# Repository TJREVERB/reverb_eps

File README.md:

# stopgap-eps
 Stopgap EPS design for TJREVERB (Not to be used as flight hardware)

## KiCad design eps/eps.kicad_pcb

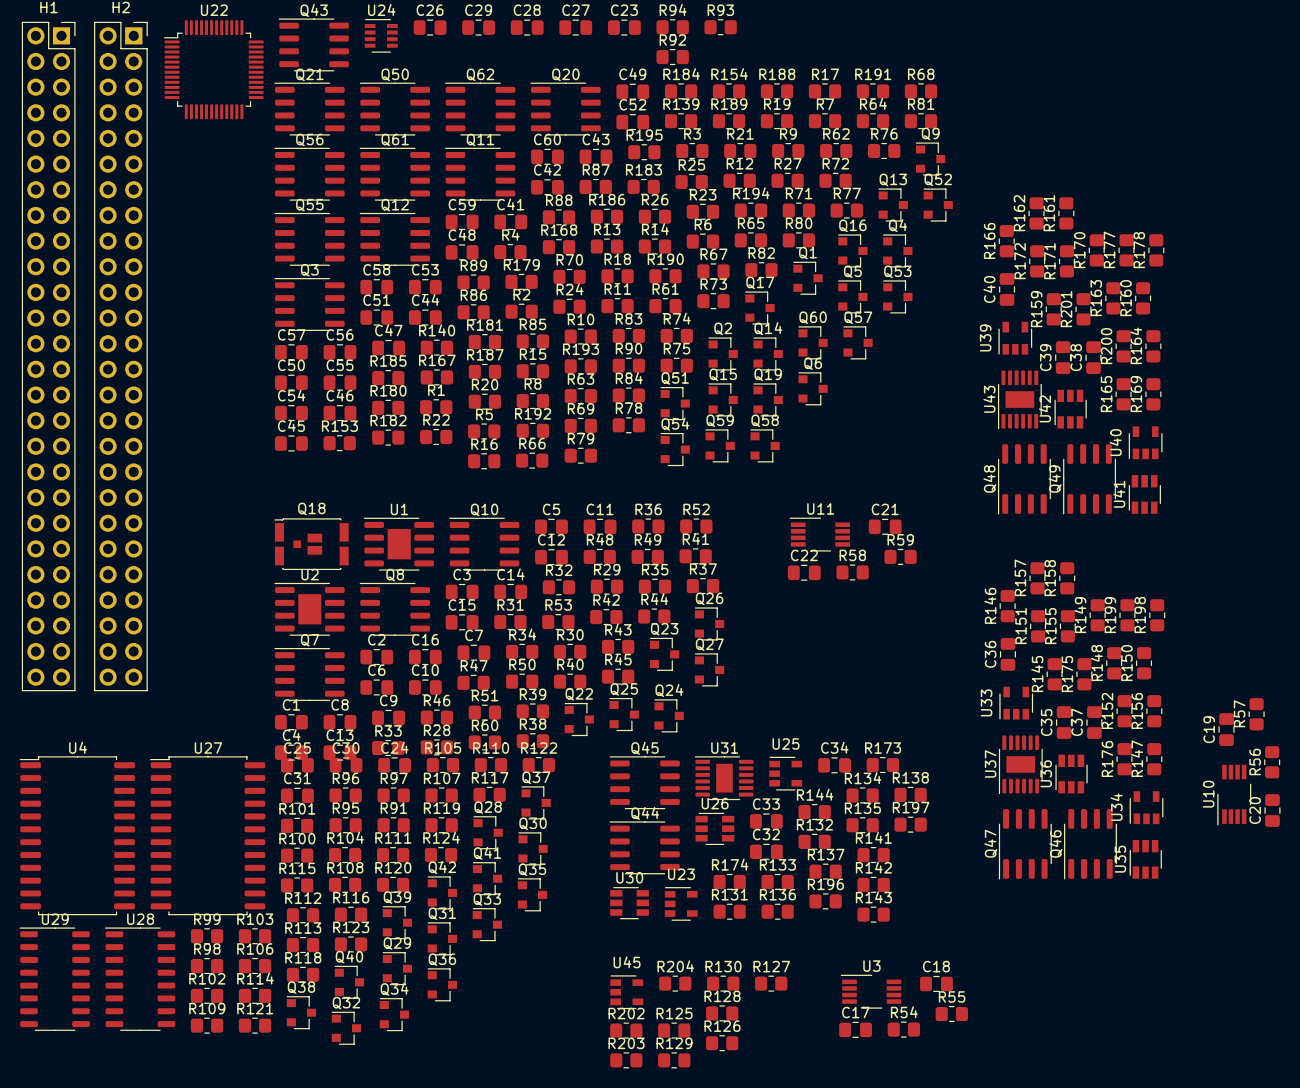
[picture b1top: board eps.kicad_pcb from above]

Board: 2 copper layers, 355 parts (0 on the bottom side), 259 nets, no tracks yet.

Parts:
C1, C2, C9, C10, C18, C20, C22, C32, C34, C35, C37, C38, C40: 10uF; C_0805_2012Metric_Pad1.18x1.45mm_HandSolder
C3, C4, C12, C13, C16, C23, C24, C25, C26, C28, C30, C31, C44, C45, C46, C50, C51, C52, C55, C56, C59, C60: 0.1uF; C_0805_2012Metric_Pad1.18x1.45mm_HandSolder
C5, C6, C7: 47uF; C_0805_2012Metric_Pad1.18x1.45mm_HandSolder
C8: 100uF; C_0805_2012Metric_Pad1.18x1.45mm_HandSolder
C11, C14, C15, C27, C29, C33, C36, C39, C41, C42, C43, C47, C48, C49, C53, C54, C57, C58: 1uF; C_0805_2012Metric_Pad1.18x1.45mm_HandSolder
C17, C19, C21: 0.01uF; C_0805_2012Metric_Pad1.18x1.45mm_HandSolder
H1: EPS Stack Header 2; PinSocket_2x26_P2.54mm_Vertical
H2: EPS Stack Header 1; PinSocket_2x26_P2.54mm_Vertical
Q1, Q2, Q4, Q5, Q6, Q9, Q13, Q14, Q15, Q16, Q17, Q19, Q22, Q23, Q24, Q25, Q26, Q27, Q51, Q52, Q53, Q54, Q57, Q58, Q59, Q60: 2N7002; SOT-23
Q3, Q7, Q8, Q10, Q11, Q12, Q20, Q21, Q43, Q44, Q45, Q46, Q47, Q48, Q49, Q50, Q55, Q56, Q61, Q62: IRF7425; SOIC-8_3.9x4.9mm_P1.27mm
Q18: IRF8302M; DirectFET_MX
Q28, Q29, Q30, Q31, Q32, Q33, Q34, Q35, Q36, Q37, Q38, Q39, Q40, Q41, Q42: IRLML6344; SOT-23
R1, R2, R4, R24, R25, R26, R82, R83, R133, R134, R147, R148, R161, R162, R180, R181, R203: 100R; R_0805_2012Metric_Pad1.20x1.40mm_HandSolder
R3, R5, R6, R7, R8, R9, R10, R11, R12, R18, R19, R20, R21, R22, R23, R27, R32, R33, R36, R37, R38, R41, R42, R46, R48, R49, R50, R51, R52, R53, R60, R62, R63, R64, R65, R66, R67, R68, R69, R76, R77, R78, R79, R80, R81, R84, R85, R86, R87, R88, R89, R92, R94, R154, R167, R168, R179, R182, R183, R184, R185, R186, R187, R192, R193, R194, R195: 10K; R_0805_2012Metric_Pad1.20x1.40mm_HandSolder
R13, R14, R43, R44, R61, R70, R71, R72, R90, R139, R188, R189: 15m; R_0805_2012Metric_Pad1.20x1.40mm_HandSolder
R15, R16, R17, R73, R74, R75, R140, R153, R190, R191: 15K; R_0805_2012Metric_Pad1.20x1.40mm_HandSolder
R28: 322K; R_0805_2012Metric_Pad1.20x1.40mm_HandSolder
R29: 678K; R_0805_2012Metric_Pad1.20x1.40mm_HandSolder
R30: 11.2M; R_0805_2012Metric_Pad1.20x1.40mm_HandSolder
R31, R39, R40, R91, R125, R126, R127, R128, R129, R130, R197, R199, R201: 100K; R_0805_2012Metric_Pad1.20x1.40mm_HandSolder
R34: 10m; R_0805_2012Metric_Pad1.20x1.40mm_HandSolder
R35: 40K; R_0805_2012Metric_Pad1.20x1.40mm_HandSolder
R45, R47: 27K; R_0805_2012Metric_Pad1.20x1.40mm_HandSolder
R54, R56, R58: 5K; R_0805_2012Metric_Pad1.20x1.40mm_HandSolder
R55, R57, R59: 45.5K; R_0805_2012Metric_Pad1.20x1.40mm_HandSolder
R93: 50K; R_0805_2012Metric_Pad1.20x1.40mm_HandSolder
R95, R99, R109, R111: 2.7K; R_0805_2012Metric_Pad1.20x1.40mm_HandSolder
R96, R98, R100, R102, R104, R106, R108, R110, R112, R114, R116, R118, R120, R122, R124, R135, R136, R149, R150, R163, R164, R204: 1K; R_0805_2012Metric_Pad1.20x1.40mm_HandSolder
R97, R105, R107: 3.9K; R_0805_2012Metric_Pad1.20x1.40mm_HandSolder
R101, R103, R113, R115, R117, R119, R121, R123: 1.2K; R_0805_2012Metric_Pad1.20x1.40mm_HandSolder
R131, R132, R145, R146, R159, R160, R202: 20m; R_0805_2012Metric_Pad1.20x1.40mm_HandSolder
R137, R138, R151, R152, R165, R166: 470K; R_0805_2012Metric_Pad1.20x1.40mm_HandSolder
R141, R155, R169: 52.8K; R_0805_2012Metric_Pad1.20x1.40mm_HandSolder
R142, R156, R170: 490K; R_0805_2012Metric_Pad1.20x1.40mm_HandSolder
R143, R157, R171: 330K; R_0805_2012Metric_Pad1.20x1.40mm_HandSolder
R144, R158, R172: 50m; R_0805_2012Metric_Pad1.20x1.40mm_HandSolder
R173, R174, R175, R176, R177, R178, R196, R198, R200: R; R_0805_2012Metric_Pad1.20x1.40mm_HandSolder
U1: ADP2303ARDZ-3.3; SOIC-8-1EP_3.9x4.9mm_P1.27mm_EP2.29x3mm
U2: ADP2303ARDZ-5.0; SOIC-8-1EP_3.9x4.9mm_P1.27mm_EP2.29x3mm
U3, U10, U11: TLC555xPS; VSSOP-8_3.0x3.0mm_P0.65mm
U4, U27: CD74HC4067M; SOIC-24W_7.5x15.4mm_P1.27mm
U22: STM32F103C8Tx; LQFP-48_7x7mm_P0.5mm
U23, U25, U33, U34, U39, U40, U45: LT6106; SOT-23-5
U24: MAX6369; SOT-23-8
U26, U30, U35, U36, U41, U42: LTC4412xS6; TSOT-23-6
U28, U29: 74HC595; SO-16_3.9x9.9mm_P1.27mm
U31, U37, U43: LT3652EMSE; MSOP-12-1EP_3x4mm_P0.65mm_EP1.65x2.85mm

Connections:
3V3RAW: C5.1, C7.1, C23.1, C24.1, C25.1, C26.1, C27.1, C30.1, C31.1, Q10.1, Q10.2, Q10.3, Q43.4, R50.1, R92.1, R94.1, U1.5, U4.24, U22.1, U22.24, U22.36, U22.48, U24.5, U24.6, U24.8, U27.24, U28.10, U28.16, U29.10, U29.16
3V3RESETPLS: R54.2, U3.2
5VRESETPLS: R56.2, U10.2
+3V3: H2.27, H2.28, Q12.1, Q12.2, Q12.3, Q50.1, Q50.2, Q50.3, Q62.1, Q62.2, Q62.3, R12.1, R44.1, R69.1, R103.1, R187.1
+5V: H2.25, H2.26, Q11.1, Q11.2, Q11.3, Q21.1, Q21.2, Q21.3, Q56.1, Q56.2, Q56.3, R11.1, R43.1, R68.1, R89.1, R101.1
+12V: H2.23, H2.24, Q3.1, Q3.2, Q3.3, Q20.1, Q20.2, Q20.3, R5.1, R67.1, R97.1
+BATT: H2.45, H2.46, Q55.1, Q55.2, Q55.3, Q61.1, Q61.2, Q61.3, R34.1, R88.1, R99.1, R186.1
/AnalogTelemetry/AMUX: U4.1, U27.1
/AnalogTelemetry/BRDTMP: R91.1, U27.16
/AnalogTelemetry/EN1: Q28.1, U28.15
/AnalogTelemetry/EN2: Q29.1, U28.1
/AnalogTelemetry/EN3: Q30.1, U28.2
/AnalogTelemetry/EN4: Q31.1, U28.3
/AnalogTelemetry/EN5: Q32.1, U28.4
/AnalogTelemetry/EN6: Q33.1, U28.5
/AnalogTelemetry/EN7: Q34.1, U28.6
/AnalogTelemetry/EN8: Q35.1, U28.7
/AnalogTelemetry/EN9: Q36.1, U29.15
/AnalogTelemetry/EN10: Q37.1, U29.1
/AnalogTelemetry/EN11: Q38.1, U29.2
/AnalogTelemetry/EN12: Q39.1, U29.3
/AnalogTelemetry/EN13: Q40.1, U29.4
/AnalogTelemetry/EN14: Q41.1, U29.5
/AnalogTelemetry/EN15: Q42.1, U29.6
/AnalogTelemetry/RCLK: U28.12, U29.12
/AnalogTelemetry/SEL0: U4.10, U27.10
/AnalogTelemetry/SEL1: U4.11, U27.11
/AnalogTelemetry/SEL2: U4.14, U27.14
/AnalogTelemetry/SEL3: U4.13, U27.13
/AnalogTelemetry/SRCLK: U28.11, U29.11
/AnalogTelemetry/VBCR_OUT: R95.2, R96.1, U4.9
/AnalogTelemetry/VPCM3V3: R103.2, R104.1, U4.5
/AnalogTelemetry/VPCM5V: R101.2, R102.1, U4.6
/AnalogTelemetry/VPCM12V: R97.2, R98.1, U4.8
/AnalogTelemetry/VPCMBATV: R99.2, R100.1, U4.7
/AnalogTelemetry/VSW1: R105.2, R106.1, U4.4
/AnalogTelemetry/VSW2: R107.2, R108.1, U4.3
/AnalogTelemetry/VSW3: R109.2, R110.1, U4.2
/AnalogTelemetry/VSW4: R111.2, R112.1, U4.23
/AnalogTelemetry/VSW5: R113.2, R114.1, U4.22
/AnalogTelemetry/VSW6: R115.2, R116.1, U4.21
/AnalogTelemetry/VSW7: R117.2, R118.1, U4.20
/AnalogTelemetry/VSW8: R119.2, R120.1, U4.19
/AnalogTelemetry/VSW9: R121.2, R122.1, U4.18
/AnalogTelemetry/VSW10: R123.2, R124.1, U4.17
/BCR/SA1AV: R131.2, R133.2, U23.5
/BCR/SA1BV: R132.2, R134.2, U25.5
/BCR/SA2AV: R145.2, R147.2, U33.5
/BCR/SA2BV: R146.2, R148.2, U34.5
/BCR/SA3AV: R159.2, R161.2, U39.5
/BCR/SA3BV: R160.2, R162.2, U40.5
/HNDSHK: R93.1, U22.19, U24.1
/PCM/3v3gate: Q25.1, U3.3
/PCM/5VGATE: Q26.1, U10.3
/PCM/BATGATE: Q27.1, R60.1, U11.3
/RESET: R94.2, U22.7, U22.18, U24.7
/TSET: R92.2, U22.39, U24.4
BATRESETPLS: R58.2, U11.2
BCR1ASTAT: R137.2, U26.4
BCR1BSTAT: R138.2, U30.4
BCR1OUT: C34.1, C37.1, C40.1, R142.1, R144.1, R156.1, R158.1, R170.1, R172.1, R202.2, R203.2, U31.9, U37.9, U43.9, U45.5
BCR2ASTAT: R151.2, U35.4
BCR2BSTAT: R152.2, U36.4
BCR3ASTAT: R165.2, U41.4
BCR3BSTAT: R166.2, U42.4
BCR_OUT: H2.41, H2.42, H2.43, H2.44, R95.1, R202.1, U45.4
GND: C1.2, C2.2, C5.2, C6.2, C7.2, C8.2, C9.2, C10.2, C11.2, C12.2, C13.2, C14.2, C15.2, C16.2, C17.2, C18.2, C19.2, C20.2, C21.2, C22.2, C23.2, C24.2, C25.2, C26.2, C27.2, C28.2, C29.2, C30.2, C31.2, C32.2, C34.2, C35.2, C37.2, C38.2, C40.2, C41.2, C42.2, C43.2, C44.1, C45.1, C46.1, C47.2, C48.2, C49.2, C50.1, C51.1, C52.1, C53.2, C54.2, C55.1, C56.1, C57.2, C58.2, C59.1, C60.1, H2.9, H2.14, H2.17, H2.21, H2.22, H2.29, H2.30, H2.32, H2.47, H2.48, Q2.2, Q5.2, Q9.2, Q14.2, Q16.2, Q19.2, Q22.2, Q23.2, Q24.2, Q25.2, Q27.2, Q28.2, Q29.2, Q30.2, Q31.2, Q32.2, Q33.2, Q34.2, Q35.2, Q36.2, Q37.2, Q38.2, Q39.2, Q40.2, Q41.2, Q42.2, Q52.2, Q54.2, Q58.2, Q60.2, R3.2, R6.2, R7.2, R21.2, R22.2, R23.2, R27.2, R28.2, R36.2, R46.2, R48.2, R60.2, R62.2, R63.2, R79.2, R80.2, R81.2, R84.2, R85.2, R91.2, R93.2, R135.2, R136.2, R143.2, R149.2, R150.2, R157.2, R163.2, R164.2, R168.2, R171.2, R179.2, R182.2, R183.2, R194.2, R195.2, R197.2, R199.2, R201.2, R204.2, U1.7, U1.9, U2.7, U2.9, U3.1, U4.12, U10.1, U11.1, U22.8, U22.23, U22.35, U22.47, U23.2, U24.2, U25.2, U26.2, U26.3, U27.12, U28.8, U28.13, U29.8, U29.13, U30.2, U30.3, U31.6, U31.13, U33.2, U34.2, U35.2, U35.3, U36.2, U36.3, U37.6, U37.13, U39.2, U40.2, U41.2, U41.3, U42.2, U42.3, U43.6, U43.13, U45.2
I3V3: R47.1, U27.5
I5V: R45.1, U27.6
IBATV: R35.1, U27.7
IBCR1A: R135.1, U23.1
IBCR1B: R136.1, U25.1
IBCR2A: R149.1, U33.1
IBCR2B: R150.1, U34.1
IBCR3A: R163.1, U39.1
IBCR3B: R164.1, U40.1
IBCR_OUT: R204.1, U27.9, U45.1
ISW1: R15.1, U27.4
ISW2: R73.1, U27.3
ISW3: R140.1, U27.2
ISW4: R190.1, U27.23
ISW5: R16.1, U27.22
ISW6: R74.1, U27.21
ISW7: R153.1, U27.20
ISW8: R191.1, U27.19
ISW9: R17.1, U27.18
ISW10: R75.1, U27.17
unnamed: C3.1, U1.1
unnamed: C3.2, U1.8
unnamed: C4.1, U2.1
unnamed: C4.2, U2.8
unnamed: C6.1, Q8.1, Q8.2, Q8.3, R49.1, U2.5
unnamed: C17.1, U3.5
unnamed: C18.1, R55.2, U3.6, U3.7
unnamed: C19.1, U10.5
unnamed: C20.1, R57.2, U10.6, U10.7
unnamed: C21.1, U11.5
unnamed: C22.1, R59.2, U11.6, U11.7
unnamed: C33.1, U31.12
unnamed: C33.2, U31.11
unnamed: C36.1, U37.12
unnamed: C36.2, U37.11
unnamed: C39.1, U43.12
unnamed: C39.2, U43.11
unnamed: R144.2, U31.10
unnamed: R158.2, U37.10
unnamed: R172.2, U43.10
unnamed: Q1.1, R1.1, R3.1
unnamed: Q1.2, Q2.3
unnamed: Q1.3, Q3.4, R5.2
unnamed: Q2.1, R8.2
unnamed: Q3.5, Q3.6, Q3.7, Q3.8, R61.2
unnamed: Q4.1, R2.1, R6.1
unnamed: Q4.2, Q5.3
unnamed: Q5.1, R9.2
unnamed: Q6.1, R4.1, R7.1
unnamed: Q6.2, Q9.3
unnamed: Q7.5, Q7.6, Q7.7, Q7.8, R34.2
unnamed: Q8.5, Q8.6, Q8.7, Q8.8, R43.2
unnamed: Q9.1, R10.2
unnamed: Q10.4, Q24.3, R50.2
unnamed: Q10.5, Q10.6, Q10.7, Q10.8, R44.2
unnamed: Q4.3, Q11.4, R11.2
unnamed: Q11.5, Q11.6, Q11.7, Q11.8, R13.2
unnamed: Q6.3, Q12.4, R12.2
unnamed: Q12.5, Q12.6, Q12.7, Q12.8, R14.2
unnamed: Q13.1, R24.1, R27.1
unnamed: Q13.2, Q14.3
unnamed: Q13.3, Q20.4, R67.2
unnamed: Q14.1, R64.2
unnamed: Q15.1, R25.1, R62.1
unnamed: Q15.2, Q16.3
unnamed: Q15.3, Q21.4, R68.2
unnamed: Q16.1, R65.2
unnamed: Q17.1, R26.1, R63.1
unnamed: Q17.2, Q19.3
unnamed: Q17.3, Q50.4, R69.2
unnamed: Q19.1, R66.2
unnamed: Q20.5, Q20.6, Q20.7, Q20.8, R70.2
unnamed: Q21.5, Q21.6, Q21.7, Q21.8, R71.2
unnamed: Q22.1, Q27.3, R38.1
unnamed: Q7.4, Q22.3, R33.2
unnamed: Q23.1, R51.1
unnamed: Q8.4, Q23.3, R49.2
unnamed: Q24.1, R42.1
unnamed: Q25.3, R39.2, R52.2, U1.3
unnamed: Q26.3, R40.1, R53.2, U2.3
unnamed: Q28.3, R96.2
unnamed: Q29.3, R98.2
unnamed: Q30.3, R100.2
unnamed: Q31.3, R102.2
unnamed: Q32.3, R104.2
unnamed: Q33.3, R106.2
unnamed: Q34.3, R108.2
unnamed: Q35.3, R110.2
unnamed: Q36.3, R112.2
unnamed: Q37.3, R114.2
unnamed: Q38.3, R116.2
unnamed: Q39.3, R118.2
unnamed: Q40.3, R120.2
unnamed: Q41.3, R122.2
unnamed: Q42.3, R124.2
unnamed: Q43.5, Q43.6, Q43.7, Q43.8, U22.9
unnamed: Q44.4, U26.5
unnamed: Q44.5, Q44.6, Q44.7, Q44.8, R131.1, U23.4, U26.1
unnamed: Q45.4, U30.5
unnamed: Q45.5, Q45.6, Q45.7, Q45.8, R132.1, U25.4, U30.1
unnamed: Q46.4, U35.5
unnamed: Q46.5, Q46.6, Q46.7, Q46.8, R145.1, U33.4, U35.1
unnamed: Q47.4, U36.5
unnamed: Q47.5, Q47.6, Q47.7, Q47.8, R146.1, U34.4, U36.1
unnamed: Q48.4, U41.5
unnamed: Q48.5, Q48.6, Q48.7, Q48.8, R159.1, U39.4, U41.1
unnamed: Q49.4, U42.5
unnamed: Q49.5, Q49.6, Q49.7, Q49.8, R160.1, U40.4, U42.1
unnamed: Q50.5, Q50.6, Q50.7, Q50.8, R72.2
unnamed: Q51.1, R82.1, R84.1
unnamed: Q51.2, Q52.3
unnamed: Q51.3, Q55.4, R88.2
unnamed: Q52.1, R86.2
unnamed: Q53.1, R83.1, R85.1
unnamed: Q53.2, Q54.3
unnamed: Q53.3, Q56.4, R89.2
unnamed: Q54.1, R87.2
unnamed: Q55.5, Q55.6, Q55.7, Q55.8, R90.2
unnamed: Q56.5, Q56.6, Q56.7, Q56.8, R139.2
unnamed: Q57.1, R180.1, R182.1
unnamed: Q57.2, Q58.3
unnamed: Q57.3, Q61.4, R186.2
unnamed: Q58.1, R184.2
unnamed: Q59.1, R181.1, R183.1
unnamed: Q59.2, Q60.3
unnamed: Q59.3, Q62.4, R187.2
unnamed: Q60.1, R185.2
unnamed: Q61.5, Q61.6, Q61.7, Q61.8, R188.2
unnamed: Q62.5, Q62.6, Q62.7, Q62.8, R189.2
unnamed: R15.2, R21.1
unnamed: R16.2, R22.1
unnamed: R17.2, R23.1
unnamed: R28.1, R29.2
unnamed: R29.1, R30.2
unnamed: R35.2, R36.1
unnamed: R39.1, U1.4
unnamed: R40.2, U2.4
unnamed: R45.2, R46.1
unnamed: R47.2, R48.1
unnamed: R73.2, R79.1
unnamed: R74.2, R80.1
unnamed: R75.2, R81.1
unnamed: R133.1, U23.3
unnamed: R134.1, U25.3
unnamed: R140.2, R168.1
unnamed: R141.1, U31.7
unnamed: R141.2, R142.2, R143.1
unnamed: R147.1, U33.3
unnamed: R148.1, U34.3
unnamed: R153.2, R179.1
unnamed: R155.1, U37.7
unnamed: R155.2, R156.2, R157.1
unnamed: R161.1, U39.3
unnamed: R162.1, U40.3
unnamed: R169.1, U43.7
unnamed: R169.2, R170.2, R171.1
unnamed: R190.2, R194.1
unnamed: R191.2, R195.1
unnamed: R196.2, R197.1, U31.2
unnamed: R198.2, R199.1, U37.2
unnamed: R200.2, R201.1, U43.2
unnamed: R203.1, U45.3
unnamed: U28.9, U29.14
PCM_IN: H2.35, H2.36, Q18.1, R30.1, R31.1
PCM_IN_FILT: C1.1, C2.1, C8.1, C9.1, Q7.1, Q7.2, Q7.3, Q18.3, R33.1, R52.1, R53.1, U1.2, U2.2
RST3V3: C15.1, R41.2
RST5V: C14.1, R37.2
RSTBATT: C11.1, R32.2
RSTSW1: C41.1, R18.2
RSTSW2: C47.1, R76.2
RSTSW3: C53.1, R154.2
RSTSW4: C57.1, R192.2
RSTSW5: C42.1, R19.2
RSTSW6: C48.1, R77.2
RSTSW7: C54.1, R167.2
RSTSW8: C58.1, R193.2
RSTSW9: C43.1, R20.2
RSTSW10: C49.1, R78.2
SW1: H2.8, R61.1, R105.1
SW2: H2.10, R70.1, R107.1
SW3: H2.11, R90.1, R109.1
SW4: H2.12, R111.1, R188.1
SW5: H2.13, R13.1, R113.1
SW6: H2.15, R71.1, R115.1
SW7: H2.16, R117.1, R139.1
SW8: H2.18, R119.1, R189.1
SW9: H2.19, R14.1, R121.1
SW10: H2.20, R72.1, R123.1
VBCR1IN: C32.1, Q44.1, Q44.2, Q44.3, Q45.1, Q45.2, Q45.3, R196.1, U26.6, U30.6, U31.1, U31.3
VBCR2IN: C35.1, Q46.1, Q46.2, Q46.3, Q47.1, Q47.2, Q47.3, R198.1, U35.6, U36.6, U37.1, U37.3
VBCR3IN: C38.1, Q48.1, Q48.2, Q48.3, Q49.1, Q49.2, Q49.3, R200.1, U41.6, U42.6, U43.1, U43.3
VCC: C10.1, C12.1, C13.1, C16.1, C28.1, C29.1, C44.2, C45.2, C46.2, C50.2, C51.2, C52.2, C55.2, C56.2, C59.2, C60.2, Q43.1, Q43.2, Q43.3, R8.1, R9.1, R10.1, R18.1, R19.1, R20.1, R32.1, R37.1, R38.2, R41.1, R42.2, R51.2, R54.1, R55.1, R56.1, R57.1, R58.1, R59.1, R64.1, R65.1, R66.1, R76.1, R77.1, R78.1, R86.1, R87.1, R125.1, R126.1, R127.1, R128.1, R129.1, R130.1, R137.1, R138.1, R151.1, R152.1, R154.1, R165.1, R166.1, R167.1, R184.1, R185.1, R192.1, R193.1, U3.4, U3.8, U10.4, U10.8, U11.4, U11.8

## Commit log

2021-10-24 fourteen mosfets
2021-10-25 24 mosfets
2021-10-25 correct p channel orientation, bias bus to be on with no input
2021-10-25 switching regs
2021-10-26 switching regulators
2021-11-02 organization
2021-11-02 implement uvp/ovp
2021-11-02 current limiters
2021-11-02 add pcm resets
2021-11-02 switch vcc to 3.3v, add battery switching mosfet
2021-11-02 add analog mux for current sense
2021-11-03 add watchdog ic and mppt ics
2021-11-03 modify mux, implement hw watchdog, standardize p channel mosfets to irf7425
2021-11-03 replace irlz44n with irf8302
2021-11-04 voltage dividers and move analog telem to new sheet
2021-11-04 bcr work
2021-11-05 start on adding LCLs to PDMs
2021-11-05 implement PDM LCLs
2021-11-13 update pcbnew
